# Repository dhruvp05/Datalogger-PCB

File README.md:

# Datalogger PCB

### Root

### Power Supply

### Microcontroller

### Relay Motor

### Digital I/O

### Layout

### 3D View

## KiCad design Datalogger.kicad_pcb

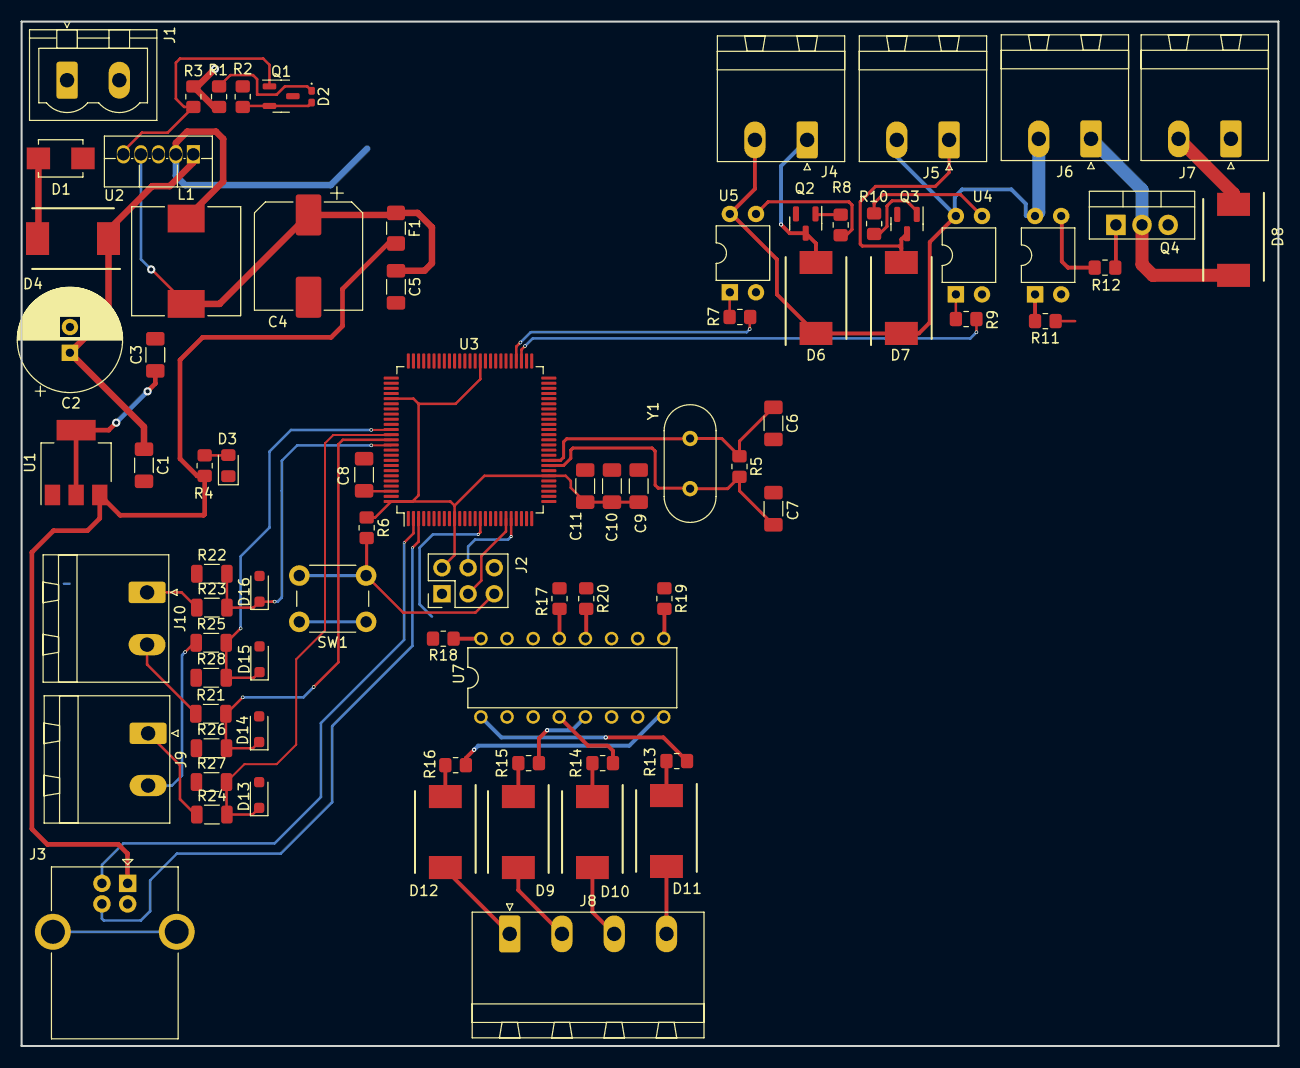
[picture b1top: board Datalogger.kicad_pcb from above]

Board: 2 copper layers, 122.2 x 99.6 mm, 80 parts (1 on the bottom side), 60 nets.

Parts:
C1, C3, C5: 10uF; C_1206_3216Metric_Pad1.33x1.80mm_HandSolder
C2: 470uF; CP_Radial_D10.0mm_P2.50mm
C4: 220uF; CP_Elec_10x10
C6, C7: 22pF; C_1206_3216Metric_Pad1.33x1.80mm_HandSolder
C8, C9, C10, C11: 104; C_1206_3216Metric_Pad1.33x1.80mm_HandSolder
D1: SMBJ12CA; DIOM4336X265N
D2: 7.5V; D_0402_1005Metric_Pad0.77x0.64mm_HandSolder
D3: LED; LED_0805_2012Metric_Pad1.15x1.40mm_HandSolder
D4, D5, D6, D7, D8, D9, D10, D11, D12: DIOM8059X256N
D13, D14, D15, D16: 5V; D_SOD-323_HandSoldering
F1: PPTC; Fuse_1206_3216Metric_Pad1.42x1.75mm_HandSolder
J1: From Mains; PhoenixContact_MSTBVA_2,5_2-G-5,08_1x02_P5.08mm_Vertical
J2: AVR-ISP-6; PinHeader_2x03_P2.54mm_Vertical
J3: USB_B; USB_B_OST_USB-B1HSxx_Horizontal
J4, J5, J6, J7, J9, J10: Screw; PhoenixContact_MSTBA_2,5_2-G-5,08_1x02_P5.08mm_Horizontal
J8: Conn_01x04_Socket; PhoenixContact_MSTBA_2,5_4-G-5,08_1x04_P5.08mm_Horizontal
L1: 68uH; L_10.4x10.4_H4.8
Q1: BC547; SOT-23-3
Q2, Q3: BC847; SOT-23
Q4: TIP127; TO-220-3_Vertical
R1, R2, R5, R6: 10k; R_0805_2012Metric_Pad1.20x1.40mm_HandSolder
R3: 47k; R_0805_2012Metric_Pad1.20x1.40mm_HandSolder
R4: 100ohm; R_0805_2012Metric_Pad1.20x1.40mm_HandSolder
R7, R8, R9, R10, R11, R12, R13, R14, R15, R16, R17, R18, R19, R20: 1k; R_0805_2012Metric_Pad1.20x1.40mm_HandSolder
R21, R22, R23, R24, R25, R26, R27, R28: 100k; R_1206_3216Metric
SW1: SW_PUSH_6mm
U1: AMS1117-3.3; SOT-223-3_TabPin2
U2: LM2596T-5; TO-220F-5_Vertical
U3: ATmega2560-16A; TQFP-100_14x14mm_P0.5mm
U4, U5, U6: PC817; DIP-4_W7.62mm
U7: CNY74-4H; DIL16
Y1: 16MHz; Crystal_HC49-4H_Vertical

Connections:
+3.3V: C3.1, U1.2 (VO)
+5V: C9.2, C10.2, C11.2, F1.2, J2.2 (VCC), J3.1 (VBUS), R4.1, R6.1, U1.3 (VI), U3.10 (VCC), U3.31 (VCC), U3.61 (VCC), U3.80 (VCC), U3.100 (AVCC), U7.10, U7.11, U7.14, U7.15
+12V: D1.1 (A1), D4.2 (A), J1.2, R1.1, R3.1
+12VA: D6.1 (K), D7.1 (K), D8.1 (K), J4.2, J5.2, J6.2, J7.2, U4.4, U5.4, U6.4
/ATMEGA2560/DIN1: R19.2, U3.66 (PJ3), U7.9
/ATMEGA2560/DIN2: R20.2, U3.67 (PJ4), U7.12
/ATMEGA2560/DIN3: R17.2, U3.68 (PJ5), U7.13
/ATMEGA2560/DIN4: R18.2, U3.69 (PJ6), U7.16
/ATMEGA2560/MTR_CTRL: R11.1, U3.15 (PH3)
/ATMEGA2560/Relay_1: R9.1, U3.53 (PC0)
/ATMEGA2560/Relay_2: R7.1, U3.54 (PC1)
AIN0: D16.1 (K), R22.2, R23.2, U3.89 (PK0)
AIN1: D14.1 (K), R21.2, R26.2, U3.88 (PK1)
AIN2: D13.1 (K), R24.2, R27.2, U3.87 (PK2)
AIN3: D15.1 (K), R25.2, R28.2, U3.86 (PK3)
GND: C1.2, C2.2, C3.2, C4.2, C5.2, C6.2, C7.2, C8.2, C9.1, C10.1, C11.1, D1.2 (A2), D3.1 (K), D5.2 (A), D13.2 (A), D14.2 (A), D15.2 (A), D16.2 (A), J1.1, J2.6 (GND), J3.4 (GND), Q1.3 (E), R2.2, R17.1, R18.1, R19.1, R20.1, R22.1, R26.1, R27.1, R28.1, SW1.1 (A), U1.1 (GND), U2.3 (GND), U3.11 (GND), U3.32 (GND), U3.62 (GND), U3.81 (GND), U3.99 (GND), U4.2, U5.2, U6.2, U7.2, U7.3, U7.6, U7.7
GND1: J7.1, Q2.2 (E), Q3.2 (E), Q4.3 (E)
MOSI: J2.4 (MOSI), U3.21 (PB2)
unnamed: D2.2 (A), Q1.2 (B), R2.1
unnamed: D2.1 (K), R1.2
unnamed: D3.2 (A), R4.2
unnamed: C1.1, C2.1, D4.1 (K), U2.1 (VIN)
unnamed: D5.1 (K), L1.1, U2.2 (OUT)
unnamed: D6.2 (A), J4.1, Q2.3 (C)
unnamed: D7.2 (A), J5.1, Q3.3 (C)
unnamed: D8.2 (A), J6.1, Q4.2 (C)
unnamed: D9.2 (A), J8.2
unnamed: D9.1 (K), R15.1
unnamed: D10.2 (A), J8.3
unnamed: D10.1 (K), R14.1
unnamed: D11.2 (A), J8.4
unnamed: D11.1 (K), R13.1
unnamed: D12.2 (A), J8.1
unnamed: D12.1 (K), R16.1
unnamed: J9.1, R24.1
unnamed: J9.2, R25.1
unnamed: J10.1, R23.1
unnamed: J10.2, R21.1
unnamed: Q2.1 (B), R8.2
unnamed: Q3.1 (B), R10.2
unnamed: Q4.1 (B), R12.2
unnamed: R7.2, U5.1
unnamed: R8.1, U5.3
unnamed: R9.2, U4.1
unnamed: R10.1, U4.3
unnamed: R11.2, U6.1
unnamed: R12.1, U6.3
unnamed: R13.2, U7.1
unnamed: R14.2, U7.4
unnamed: R15.2, U7.5
unnamed: R16.2, U7.8
unnamed: C4.1, C5.1, F1.1, L1.2, U2.4 (FB)
unnamed: C8.1, U3.98 (AREF)
unnamed: C6.1, R5.1, U3.34 (XTAL1), Y1.2
unnamed: C7.1, R5.2, U3.33 (XTAL2), Y1.1
ON/OFF: Q1.1 (C), R3.2, U2.5 (~ON/OFF)
PROG_RX0: J3.2 (D-), U3.2 (PE0)
PROG_TX0: J3.3 (D+), U3.3 (PE1)
RST: J2.5 (~RST), R6.2, SW1.2 (B), U3.30 (~RESET)
SCK: J2.3 (SCK), U3.20 (PB1)

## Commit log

2024-03-26 Initial commit with power supply and microcontroller layout
2024-03-28 "Resolved the issue of SS34 diode footprint. Problem was the pin on the downloaded footprint were not numbered
2024-03-29 Added DC motor driver
2024-04-01 Designed circuit for reading digital input. CHY74 (4 channel optocoupler) used
2024-04-28 pictures
2024-04-28 layout and 3d view pictures
2024-04-28 Analog input schematic
2024-05-19 Schematic of 4-20mA sensor
